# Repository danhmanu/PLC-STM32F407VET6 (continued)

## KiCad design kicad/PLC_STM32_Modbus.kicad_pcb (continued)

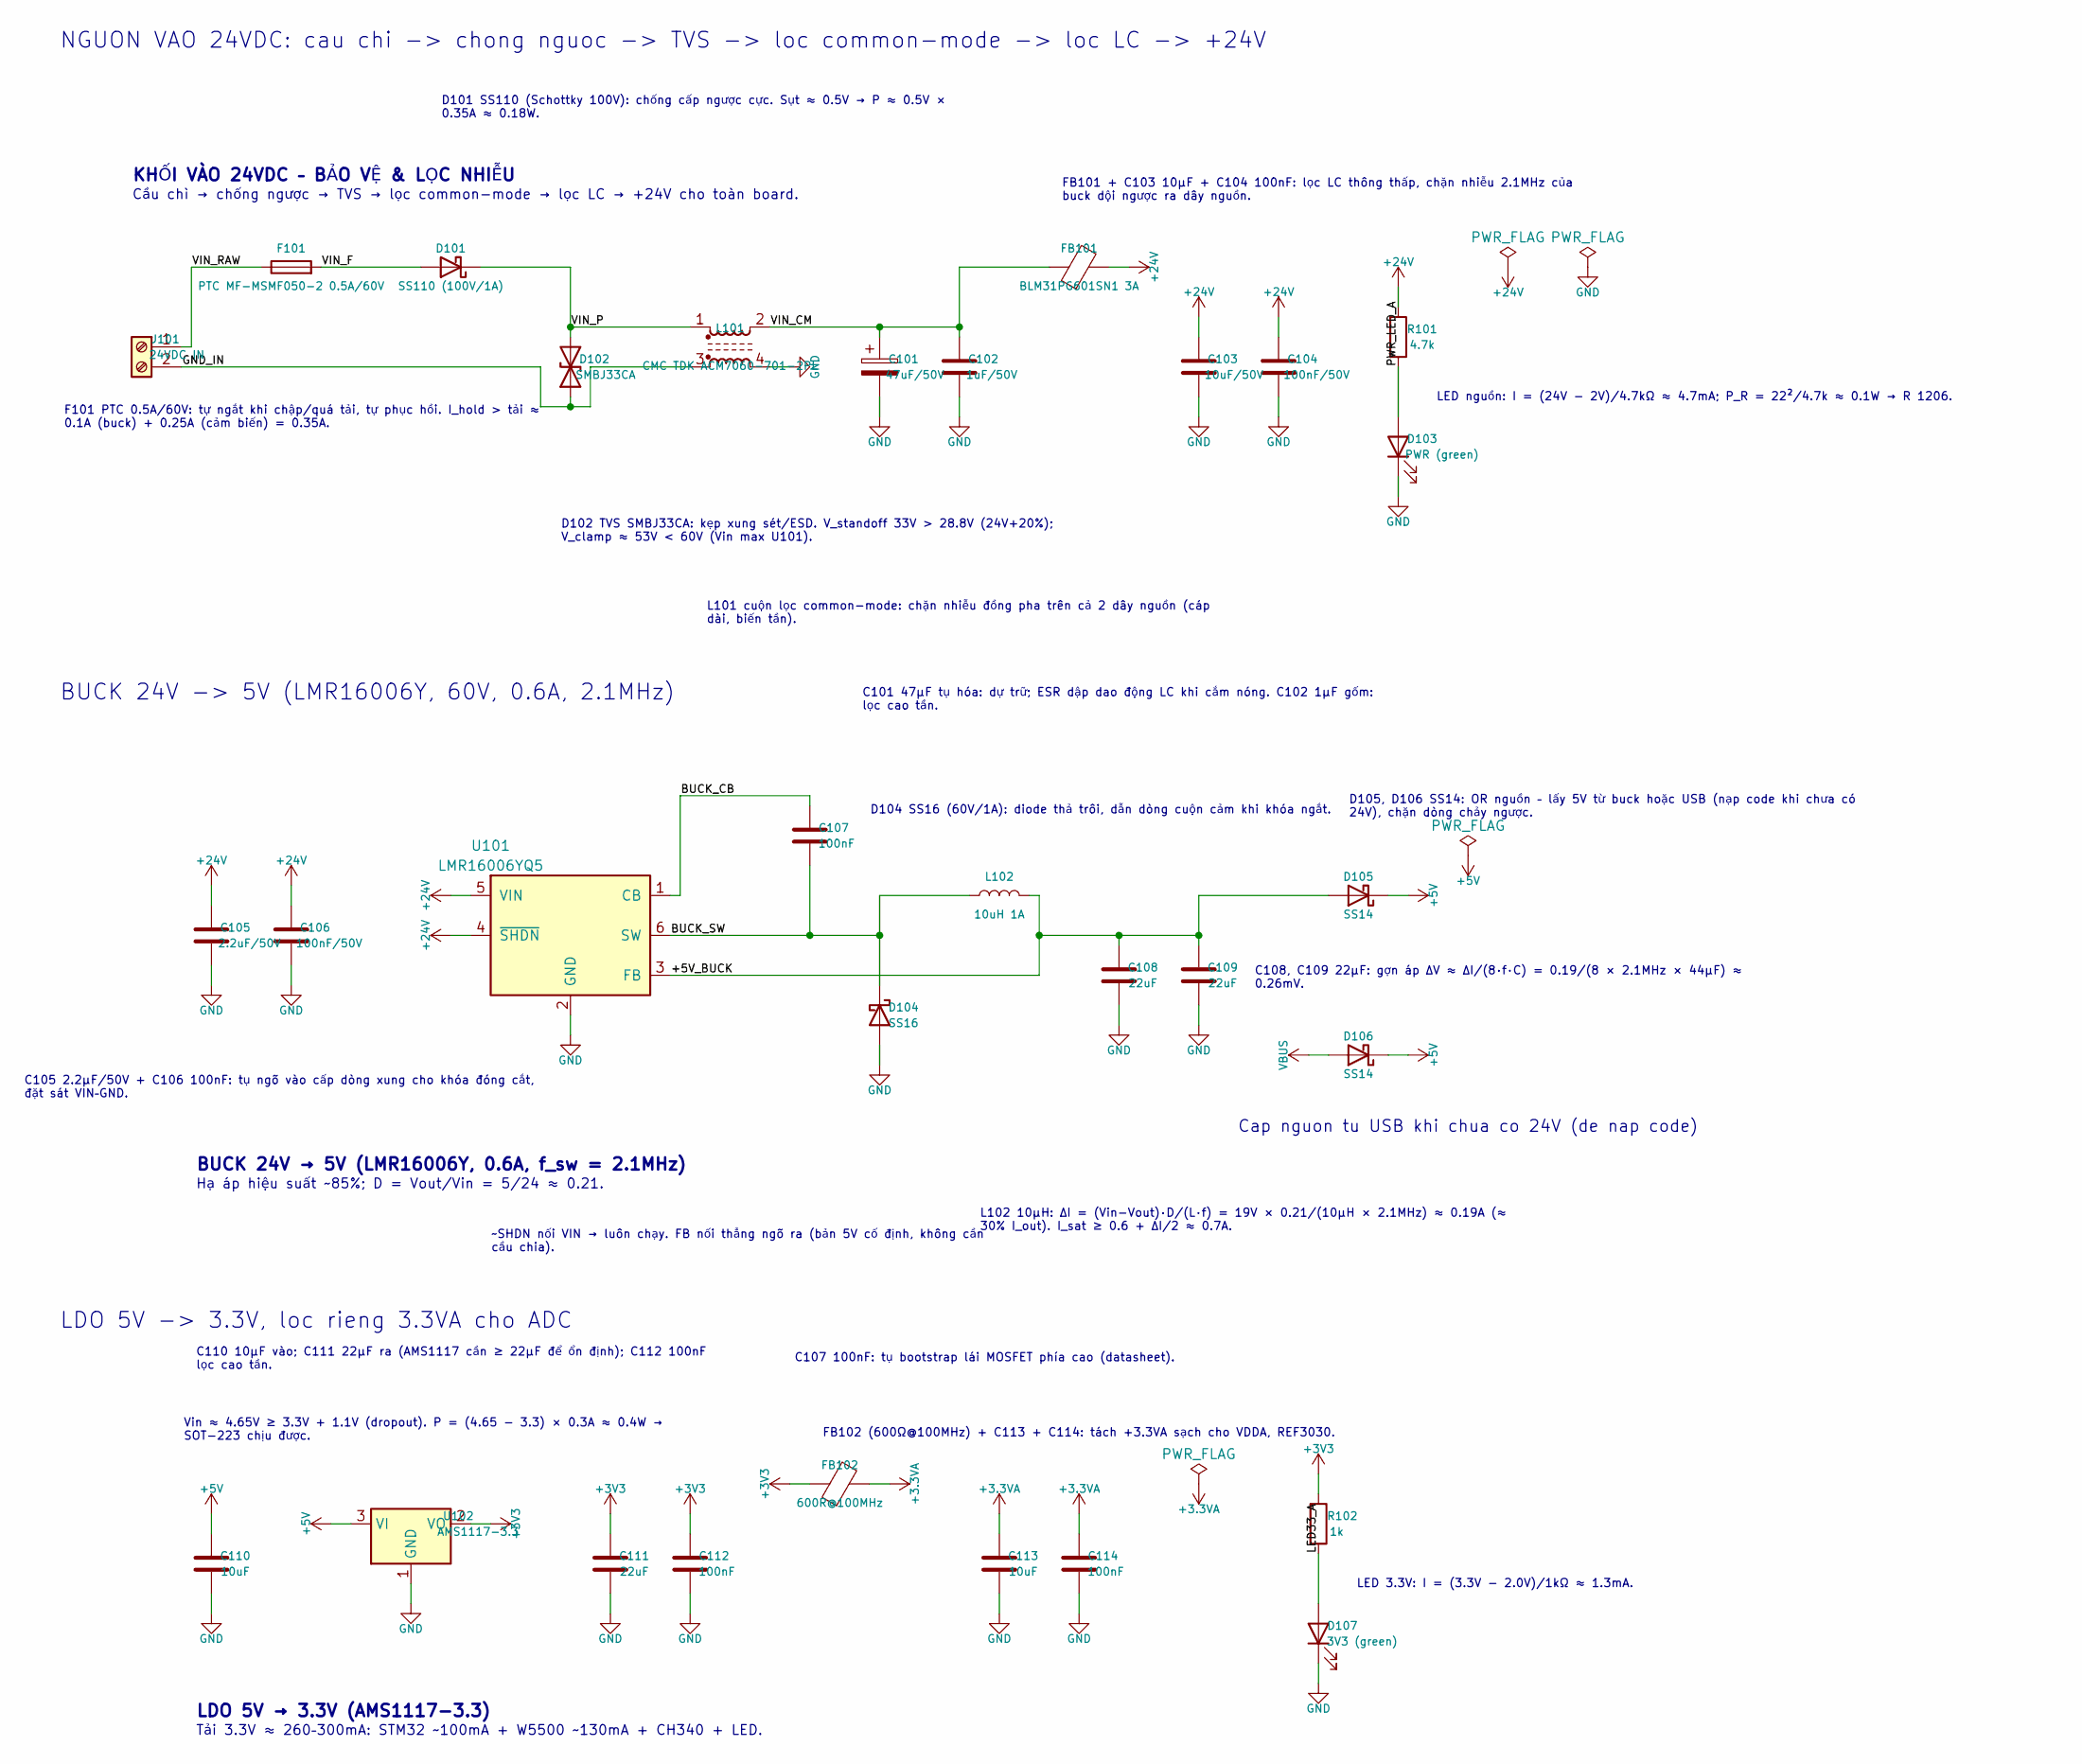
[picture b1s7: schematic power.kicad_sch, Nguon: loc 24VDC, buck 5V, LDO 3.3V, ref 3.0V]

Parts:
C101: 47uF/50V; CP_Elec_6.3x7.7
C102: 1uF/50V; C_1206_3216Metric
C103: 10uF/50V; C_1210_3225Metric
C104, C106: 100nF/50V; C_0805_2012Metric
C105: 2.2uF/50V; C_1206_3216Metric
C107, C112, C114: 100nF; C_0603_1608Metric
C108, C109, C111: 22uF; C_1206_3216Metric
C110, C113: 10uF; C_0805_2012Metric
D101: SS110 (100V/1A); D_SMA
D102: SMBJ33CA; D_SMB
D103: PWR (green); LED_0603_1608Metric
D104: SS16; D_SMA
D105, D106: SS14; D_SMA
D107: 3V3 (green); LED_0603_1608Metric
F101: PTC MF-MSMF050-2 0.5A/60V; Fuse_1812_4532Metric
FB101: BLM31PG601SN1 3A; L_1206_3216Metric
FB102: 600R@100MHz; L_0805_2012Metric
J101: 24VDC IN; TerminalBlock_Phoenix_MKDS-1-2-3.81_1x02_P3.81mm_Horizontal
L101: CMC TDK ACM7060-701-2PL; L_CommonModeChoke_TDK_ACM7060
L102: 10uH 1A; L_Bourns-SRN4018
R101: 4.7k; R_1206_3216Metric
R102: 1k; R_0603_1608Metric
U101: LMR16006YQ5; SOT-23-6
U102: AMS1117-3.3; SOT-223-3_TabPin2

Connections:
+3.3VA: C113.1, C114.1, FB102.2; also elsewhere on the board
+3V3: C111.1, C112.1, FB102.1, R102.1, U102.2 (VO); also elsewhere on the board
+5V: C110.1, D105.1 (K), D106.1 (K), U102.3 (VI)
+24V: C103.1, C104.1, C105.1, C106.1, FB101.2, R101.1, U101.4 (~SHDN), U101.5 (VIN); also elsewhere on the board
/Nguon 24VDC/+5V_BUCK: C108.1, C109.1, D105.2 (A), L102.2, U101.3 (FB)
/Nguon 24VDC/BUCK_CB: C107.1, U101.1 (CB)
/Nguon 24VDC/BUCK_SW: C107.2, D104.1 (K), L102.1, U101.6 (SW)
/Nguon 24VDC/GND_IN: D102.1 (A1), J101.2, L101.3
/Nguon 24VDC/LED33_A: D107.2 (A), R102.2
/Nguon 24VDC/PWR_LED_A: D103.2 (A), R101.2
/Nguon 24VDC/VIN_CM: C101.1, C102.1, FB101.1, L101.2
/Nguon 24VDC/VIN_F: D101.2 (A), F101.2
/Nguon 24VDC/VIN_P: D101.1 (K), D102.2 (A2), L101.1
/Nguon 24VDC/VIN_RAW: F101.1, J101.1
GND: C101.2, C102.2, C103.2, C104.2, C105.2, C106.2, C108.2, C109.2, C110.2, C111.2, C112.2, C113.2, C114.2, D103.1 (K), D104.2 (A), D107.1 (K), L101.4, U101.2 (GND), U102.1 (GND); also elsewhere on the board
VBUS: D106.2 (A); also elsewhere on the board

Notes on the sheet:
~SHDN nối VIN → luôn chạy. FB nối thẳng ngõ ra (bản 5V cố định, không cần cầu chia).
LDO 5V → 3.3V (AMS1117-3.3)
KHỐI VÀO 24VDC – BẢO VỆ & LỌC NHIỄU
LED nguồn: I = (24V − 2V)/4.7kΩ ≈ 4.7mA; P_R = 22²/4.7k ≈ 0.1W → R 1206.
Cap nguon tu USB khi chua co 24V (de nap code)
D105, D106 SS14: OR nguồn – lấy 5V từ buck hoặc USB (nạp code khi chưa có 24V), chặn dòng chảy ngược.
C101 47µF tụ hóa: dự trữ; ESR dập dao động LC khi cắm nóng. C102 1µF gốm: lọc cao tần.
LDO 5V -> 3.3V, loc rieng 3.3VA cho ADC
BUCK 24V → 5V (LMR16006Y, 0.6A, f_sw = 2.1MHz)
L101 cuộn lọc common-mode: chặn nhiễu đồng pha trên cả 2 dây nguồn (cáp dài, biến tần).
FB101 + C103 10µF + C104 100nF: lọc LC thông thấp, chặn nhiễu 2.1MHz của buck dội ngược ra dây nguồn.
F101 PTC 0.5A/60V: tự ngắt khi chập/quá tải, tự phục hồi. I_hold > tải ≈ 0.1A (buck) + 0.25A (cảm biến) = 0.35A.
D104 SS16 (60V/1A): diode thả trôi, dẫn dòng cuộn cảm khi khóa ngắt.
Hạ áp hiệu suất ~85%; D = Vout/Vin = 5/24 ≈ 0.21.
C105 2.2µF/50V + C106 100nF: tụ ngõ vào cấp dòng xung cho khóa đóng cắt, đặt sát VIN–GND.
D102 TVS SMBJ33CA: kẹp xung sét/ESD. V_standoff 33V > 28.8V (24V+20%); V_clamp ≈ 53V < 60V (Vin max U101).
C108, C109 22µF: gợn áp ΔV ≈ ΔI/(8·f·C) = 0.19/(8 × 2.1MHz × 44µF) ≈ 0.26mV.
Cầu chì → chống ngược → TVS → lọc common-mode → lọc LC → +24V cho toàn board.
Tải 3.3V ≈ 260–300mA: STM32 ~100mA + W5500 ~130mA + CH340 + LED.
FB102 (600Ω@100MHz) + C113 + C114: tách +3.3VA sạch cho VDDA, REF3030.
BUCK 24V -> 5V (LMR16006Y, 60V, 0.6A, 2.1MHz)
NGUON VAO 24VDC: cau chi -> chong nguoc -> TVS -> loc common-mode -> loc LC -> +24V
C107 100nF: tụ bootstrap lái MOSFET phía cao (datasheet).
L102 10µH: ΔI = (Vin−Vout)·D/(L·f) = 19V × 0.21/(10µH × 2.1MHz) ≈ 0.19A (≈ 30% I_out). I_sat ≥ 0.6 + ΔI/2 ≈ 0.7A.
D101 SS110 (Schottky 100V): chống cấp ngược cực. Sụt ≈ 0.5V → P ≈ 0.5V × 0.35A ≈ 0.18W.
C110 10µF vào; C111 22µF ra (AMS1117 cần ≥ 22µF để ổn định); C112 100nF lọc cao tần.
Vin ≈ 4.65V ≥ 3.3V + 1.1V (dropout). P = (4.65 − 3.3) × 0.3A ≈ 0.4W → SOT-223 chịu được.
LED 3.3V: I = (3.3V − 2.0V)/1kΩ ≈ 1.3mA.

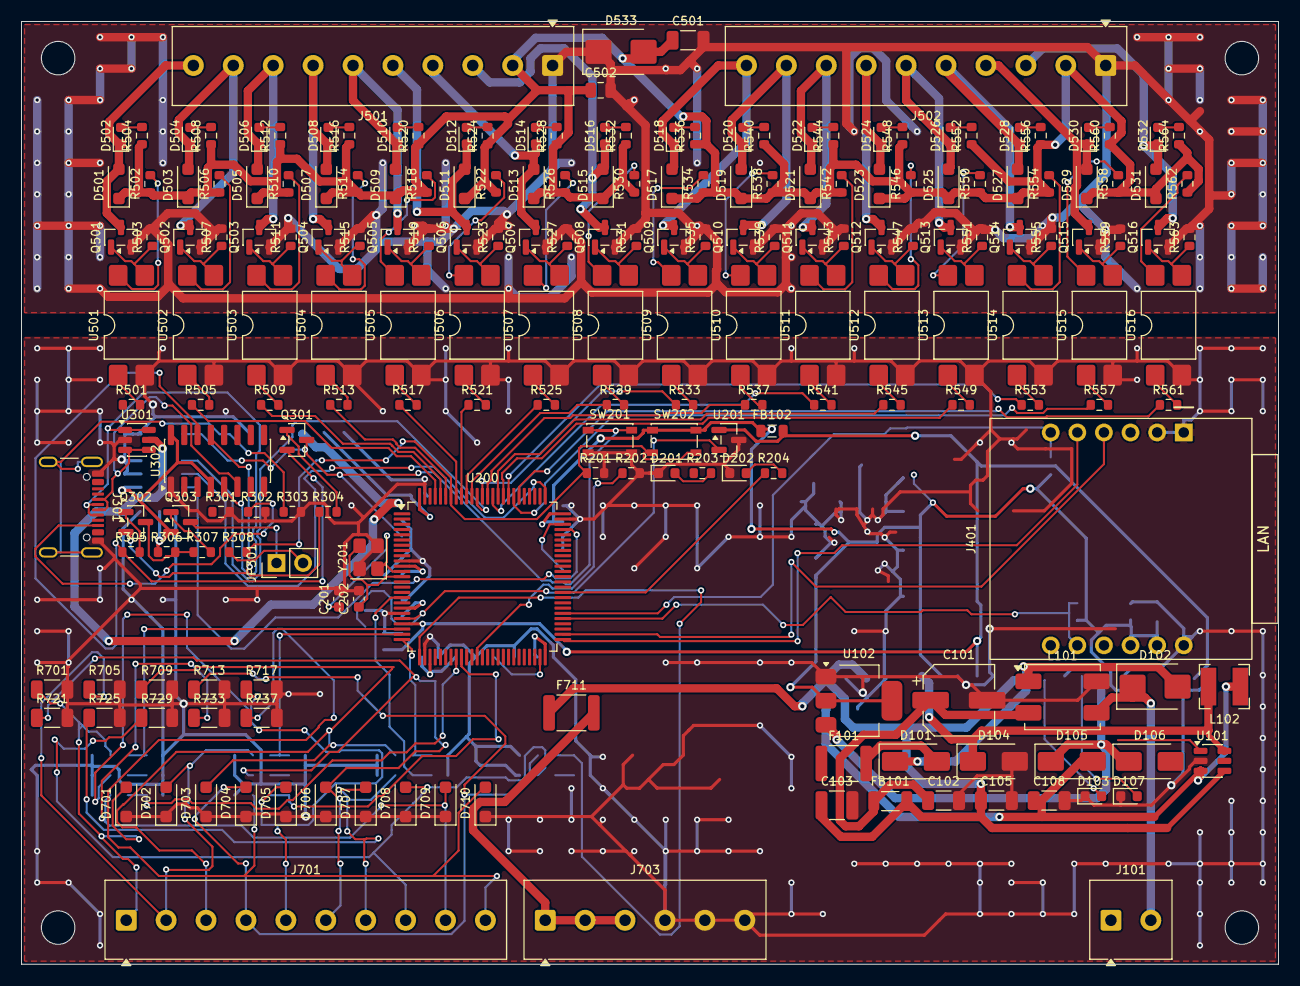
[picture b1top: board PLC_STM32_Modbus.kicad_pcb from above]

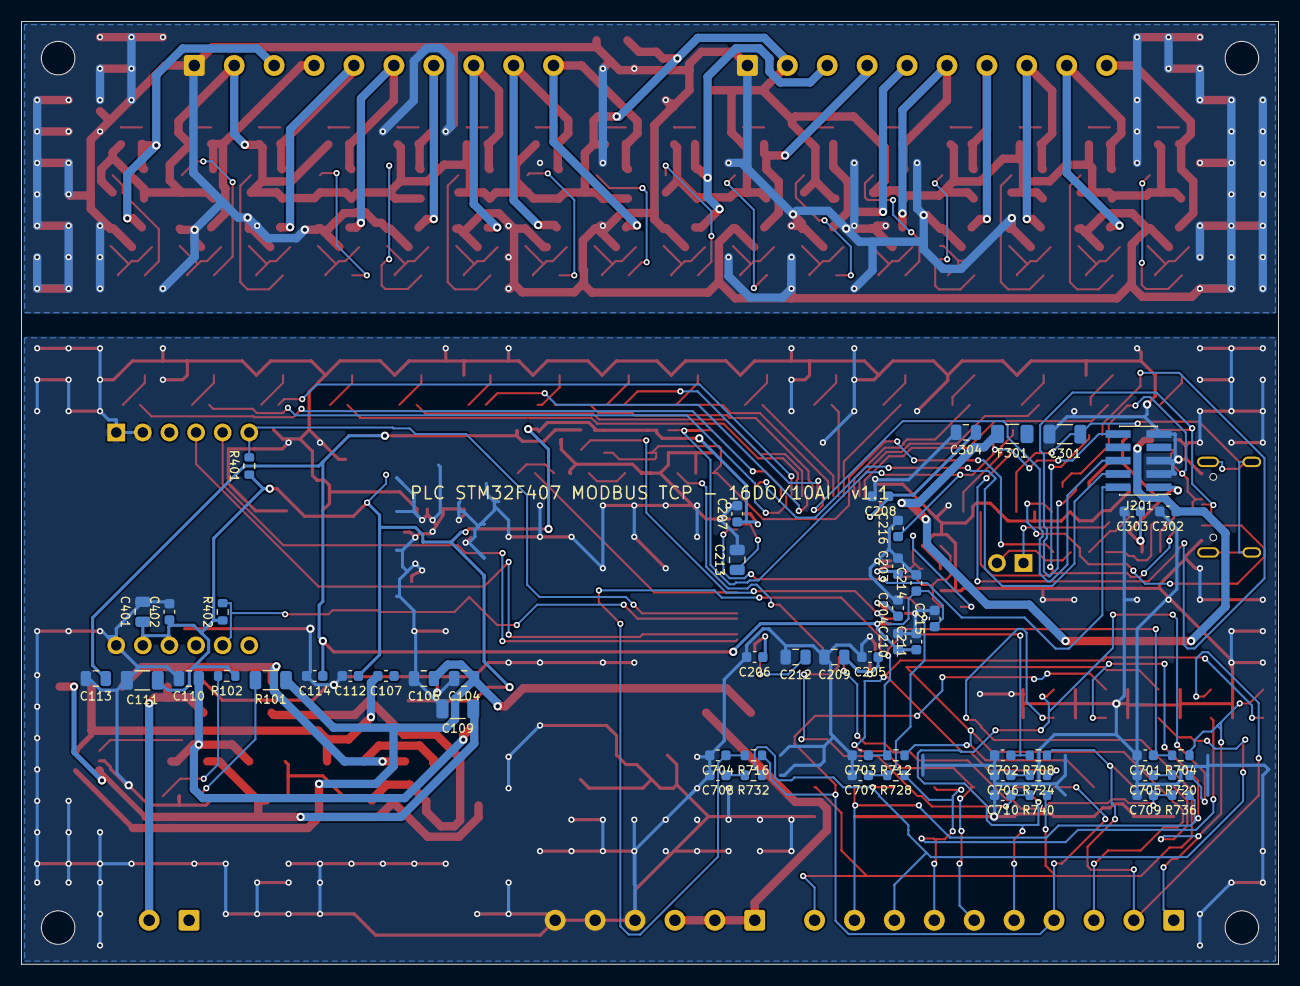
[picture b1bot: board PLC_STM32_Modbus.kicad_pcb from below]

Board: 2 copper layers, 120.0 x 90.0 mm, 264 parts (55 on the bottom side), 172 nets.

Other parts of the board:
H1, H2, H3, H4: MountingHole_3.2mm_M3

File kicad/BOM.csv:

"Ref","Value","Footprint","Qty"
"C101","47uF/50V","Capacitor_SMD:CP_Elec_6.3x7.7","1"
"C102","1uF/50V","Capacitor_SMD:C_1206_3216Metric","1"
"C103","10uF/50V","Capacitor_SMD:C_1210_3225Metric","1"
"C104,C106,C502","100nF/50V","Capacitor_SMD:C_0805_2012Metric","3"
"C105","2.2uF/50V","Capacitor_SMD:C_1206_3216Metric","1"
"C107,C112,C114,C203-C208,C211,C215,C216,C303,C402,C701-C710","100nF","Capacitor_SMD:C_0603_1608Metric","24"
"C108,C109,C111","22uF","Capacitor_SMD:C_1206_3216Metric","3"
"C110,C113,C304,C401","10uF","Capacitor_SMD:C_0805_2012Metric","4"
"C201,C202","20pF","Capacitor_SMD:C_0603_1608Metric","2"
"C209","4.7uF","Capacitor_SMD:C_0805_2012Metric","1"
"C210,C214,C302","1uF","Capacitor_SMD:C_0603_1608Metric","3"
"C212,C213","2.2uF","Capacitor_SMD:C_0805_2012Metric","2"
"C301","4.7nF/250V","Capacitor_SMD:C_1206_3216Metric","1"
"C501","10uF/50V","Capacitor_SMD:C_1206_3216Metric","1"
"D101","SS110 (100V/1A)","Diode_SMD:D_SMA","1"
"D102","SMBJ33CA","Diode_SMD:D_SMB","1"
"D103","PWR (green)","LED_SMD:LED_0603_1608Metric","1"
"D104","SS16","Diode_SMD:D_SMA","1"
"D105,D106","SS14","Diode_SMD:D_SMA","2"
"D107","3V3 (green)","LED_SMD:LED_0603_1608Metric","1"
"D201","RUN (green)","LED_SMD:LED_0603_1608Metric","1"
"D202","ERR (red)","LED_SMD:LED_0603_1608Metric","1"
"D501,D503,D505,D507,D509,D511,D513,D515,D517,D519,D521,D523,D525,D527,D529,D531","SS16FL","Diode_SMD:D_SOD-123F","16"
"D502","Q1","LED_SMD:LED_0603_1608Metric","1"
"D504","Q2","LED_SMD:LED_0603_1608Metric","1"
"D506","Q3","LED_SMD:LED_0603_1608Metric","1"
"D508","Q4","LED_SMD:LED_0603_1608Metric","1"
"D510","Q5","LED_SMD:LED_0603_1608Metric","1"
"D512","Q6","LED_SMD:LED_0603_1608Metric","1"
"D514","Q7","LED_SMD:LED_0603_1608Metric","1"
"D516","Q8","LED_SMD:LED_0603_1608Metric","1"
"D518","Q9","LED_SMD:LED_0603_1608Metric","1"
"D520","Q10","LED_SMD:LED_0603_1608Metric","1"
"D522","Q11","LED_SMD:LED_0603_1608Metric","1"
"D524","Q12","LED_SMD:LED_0603_1608Metric","1"
"D526","Q13","LED_SMD:LED_0603_1608Metric","1"
"D528","Q14","LED_SMD:LED_0603_1608Metric","1"
"D530","Q15","LED_SMD:LED_0603_1608Metric","1"
"D532","Q16","LED_SMD:LED_0603_1608Metric","1"
"D533","SMBJ33A","Diode_SMD:D_SMB","1"
"D701-D710","SMF5.0CA","Diode_SMD:D_SOD-123F","10"
"F101","PTC MF-MSMF050-2 0.5A/60V","Fuse:Fuse_1812_4532Metric","1"
"F301","500mA","Fuse:Fuse_1206_3216Metric","1"
"F711","MF-MSMF050-2 0.5A/60V","Fuse:Fuse_1812_4532Metric","1"
"FB101","BLM31PG601SN1 3A","Inductor_SMD:L_1206_3216Metric","1"
"FB102","600R@100MHz","Inductor_SMD:L_0805_2012Metric","1"
"J101","24VDC IN","TerminalBlock_Phoenix:TerminalBlock_Phoenix_MKDS-1-2-3.81_1x02_P3.81mm_Horizontal","1"
"J201","SWD","Connector_PinHeader_1.27mm:PinHeader_2x05_P1.27mm_Vertical_SMD","1"
"J301","USB-C","Connector_USB:USB_C_Receptacle_GCT_USB4105-xx-A_16P_TopMnt_Horizontal","1"
"J401","W5500 Lite module","PLC:W5500_Lite_Module","1"
"J501","OUT 1-8","TerminalBlock_Phoenix:TerminalBlock_Phoenix_MKDS-1-10-3.81_1x10_P3.81mm_Horizontal","1"
"J502","OUT 9-16","TerminalBlock_Phoenix:TerminalBlock_Phoenix_MKDS-1-10-3.81_1x10_P3.81mm_Horizontal","1"
"J701","AI 1-10 (4-20mA)","TerminalBlock_Phoenix:TerminalBlock_Phoenix_MKDS-1-10-3.81_1x10_P3.81mm_Horizontal","1"
"J703","AI PWR/COM","TerminalBlock_Phoenix:TerminalBlock_Phoenix_MKDS-1-6-3.81_1x06_P3.81mm_Horizontal","1"
"JP301","AUTO-BOOT","Connector_PinHeader_2.54mm:PinHeader_1x02_P2.54mm_Vertical","1"
"L101","CMC TDK ACM7060-701-2PL","Inductor_SMD:L_CommonModeChoke_TDK_ACM7060","1"
"L102","10uH 1A","Inductor_SMD:L_Bourns-SRN4018","1"
"Q301,Q302","MMBT3904","Package_TO_SOT_SMD:SOT-23","2"
"Q303","MMBT3906","Package_TO_SOT_SMD:SOT-23","1"
"Q501-Q516","DMN6075S","Package_TO_SOT_SMD:SOT-23","16"
"R101","4.7k","Resistor_SMD:R_1206_3216Metric","1"
"R102,R203,R204,R308","1k","Resistor_SMD:R_0603_1608Metric","4"
"R201,R202,R304-R307,R401,R402,R502-R504,R506-R508,R510-R512,R514-R516,R518-R520,R522-R524,R526-R528,R530-R532,R534-R536,R538-R540,R542-R544,R546-R548,R550-R552,R554-R556,R558-R560,R562-R564","10k","Resistor_SMD:R_0603_1608Metric","56"
"R301,R302","5.1k","Resistor_SMD:R_0603_1608Metric","2"
"R303","1M","Resistor_SMD:R_0603_1608Metric","1"
"R501,R505,R509,R513,R517,R521,R525,R529,R533,R537,R541,R545,R549,R553,R557,R561","470","Resistor_SMD:R_0603_1608Metric","16"
"R701,R705,R709,R713,R717,R721,R725,R729,R733,R737","120 0.1% 25ppm","Resistor_SMD:R_1206_3216Metric","10"
"R704,R708,R712,R716,R720,R724,R728,R732,R736,R740","4.7k","Resistor_SMD:R_0603_1608Metric","10"
"SW201","RESET","Button_Switch_SMD:SW_SPST_PTS810","1"
"SW202","BOOT","Button_Switch_SMD:SW_SPST_PTS810","1"
"U101","LMR16006YQ5","Package_TO_SOT_SMD:SOT-23-6","1"
"U102","AMS1117-3.3","Package_TO_SOT_SMD:SOT-223-3_TabPin2","1"
"U200","STM32F407VET6","Package_QFP:LQFP-100_14x14mm_P0.5mm","1"
"U201","REF3030","Package_TO_SOT_SMD:SOT-23","1"
"U301","USBLC6-2SC6","Package_TO_SOT_SMD:SOT-23-6","1"
"U302","CH340C","Package_SO:SOIC-16_3.9x9.9mm_P1.27mm","1"
"U501-U516","PC817 (SMD)","Package_DIP:SMDIP-4_W9.53mm","16"
"Y201","8MHz 20pF","Crystal:Crystal_SMD_3225-4Pin_3.2x2.5mm","1"

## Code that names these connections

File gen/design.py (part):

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def sheet_mcu():
    sh = Sheet("MCU STM32F407VET6", "mcu.kicad_sch", "Vi dieu khien STM32F407VET6")
    X, Y = 200, 150
    # DO1..DO16 = PE1, PE0, PB9, PB8, PB7, PB6, PB5, PB4, PD7..PD0 (canh tren LQFP, huong ve khoi ngo ra)
    DO_PINS = [98, 97, 96, 95, 93, 92, 91, 90, 88, 87, 86, 85, 84, 83, 82, 81]
    AI_PINS = [23, 24, 25, 26, 15, 16, 17, 18, 33, 34]                      # PA0-3, PC0-5
    conns = {6: "+3V3", 11: "+3V3", 19: "+3V3", 28: "+3V3", 50: "+3V3", 75: "+3V3", 100: "+3V3",
             10: "GND", 20: "GND", 22: "+3.3VA", 21: "VREF_3V0", 49: "VCAP1", 73: "VCAP2",
             12: "OSC_IN", 13: "OSC_OUT", 14: "NRST", 94: "BOOT0", 37: "BOOT1",
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            conns[p] = "NC"
    sh.place("MCU_ST_STM32F4:STM32F407VETx", "U200", "STM32F407VET6", X, Y, 0, conns, stub=5.08)

    # HSE 8 MHz: sat chan PH0/PH1 (canh trai MCU)
    sh.text(120, 92, "HSE 8MHz", 1.5)
    sh.place("Device:Crystal_GND24", ref("Y", 200), "8MHz 20pF", 152.4, 104.14, 90,
             {1: "OSC_IN", 3: "OSC_OUT", 2: "GND"}, footprint=fp_ok("Crystal:Crystal_SMD_3225-4Pin_3.2x2.5mm"))
    C(sh, 200, "20pF", 137.16, 99.06, "OSC_IN", "GND")
    C(sh, 200, "20pF", 137.16, 114.3, "OSC_OUT", "GND")

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    sh.place("Switch:SW_Push", ref("SW", 200), "RESET", 55.88, 48.26, 0, {1: "NRST", 2: "GND"}, footprint=fp_ok(BTN))
    R(sh, 200, "10k", 81.28, 50.8, "BOOT0", "GND")
    sh.place("Switch:SW_Push", ref("SW", 200), "BOOT", 101.6, 48.26, 0, {1: "+3V3", 2: "BOOT0"}, footprint=fp_ok(BTN))
    # BOOT1 (PB2, canh phai)
    R(sh, 200, "10k", 243.84, 142.24, "BOOT1", "GND")

    # SWD (canh phai, quay ve phia MCU)
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             {1: "+3V3", 2: "SWDIO", 3: "GND", 4: "SWCLK", 6: "SWO", 7: "NC", 8: "NC", 9: "GND", 10: "NRST"},
             footprint=fp_ok("Connector_PinHeader_1.27mm:PinHeader_2x05_P1.27mm_Vertical_SMD"), mirror="y")

    # LED trang thai (PD12/PD13, canh trai)
    sh.text(120, 172, "LED trang thai", 1.5)
    R(sh, 200, "1k", 160.02, 182.88, "LED_RUN", "RUN_A", rot=270)
    LED(sh, 200, "RUN (green)", 147.32, 182.88, "RUN_A", "GND", rot=0)
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    LED(sh, 200, "ERR (red)", 147.32, 190.5, "ERR_A", "GND", rot=0)

    sh.text(290, 160, "GAN CHAN:", 1.8)
    notes = ["DO1..DO16 -> PE1,PE0,PB9,PB8,PB7,PB6,PB5,PB4,PD7..PD0",
             "PA0-PA3, PC0-PC5 -> AI1..AI10 (ADC1 12-bit)",
             "SPI2 PB12(CS) PB13 PB14 PB15 -> W5500, PD8 RST, PD9 INT",
             "USART1 PA9/PA10 -> CH340C (bootloader UART)",
             "PA13/PA14/PB3 -> SWD, PD12/PD13 -> LED"]
    for i, n in enumerate(notes):
        sh.text(290, 167 + i * 6, n, 1.5)
    return sh
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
